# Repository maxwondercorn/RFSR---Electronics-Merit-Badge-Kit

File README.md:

Electronics Merit Badge Kit
==================================

Small ATtiny (Arduino IDE Compatible) microcontroller based kit used to teach Electronics Merit Badge at Resica Falls Scout Reservation.  Once assembled and functional, the kit allows selection of various LED display modes (Flickering Candle, Nightlight, Flashlight, Etc.) by rotating the on-board potentiometer.  Kit design is intended to meet all relevant badge requirements and expose scouts to a variety of component types at the lowest cost possible.

Repository Contents
-------------------

* **/Hardware** - Eagle Schematic / PCB Layouts & Bill Of Materials
    - PCB silkscreen periodically updated to match summer camp staff members currently teaching Electronics Merit Badge at Resica Falls Scout Reservation.
    - Bill Of Materials includes vendors / part numbers from the last production run.
* **/Software** - Demo Arduino sketch for the kit.  Code is intended to be easy to understand for beginners.
* **/Images** - Images of the kit, both assembled and in parts.

Firmware Programming
-------------------

As of the 2017 summer camp season, kit firmware is programmed using the following tools:

#### Hardware
An [Arduino Uno](https://store.arduino.cc/usa/arduino-uno-rev3) and an [AVR Programmer Shield](http://www.electrodragon.com/w/AVR_Programmer_Arduino_Shield) with ZIF socket.

Image of programming rig: [/Images/ElectronicsMBProgrammingRig.jpg](https://raw.githubusercontent.com/crossfireprod/RFSR---Electronics-Merit-Badge-Kit/master/Images/ElectronicsMBProgrammingRig.jpg)

#### Software
The Arduino Uno is used as an in system programmer (ISP) through use of the [ArduinoISP](https://github.com/arduino/ArduinoISP) sketch packaged with [Arduino 1.8.3](https://www.arduino.cc/en/main/software) to program the ATtiny 45/85 targets.  ATtiny core files available from [David Mellis' GitHub Repository](https://github.com/damellis/attiny), using [full instructions published by high-low tech](http://highlowtech.org/?p=1695) allow the ATtiny AVR microcontrollers used in the kits to be programmed directly from the Arduino IDE.

License
-------------------

All contents of this repository are released under [Creative Commons Share-alike 4.0](http://creativecommons.org/licenses/by-sa/4.0/).

Kit Design By: [*ZachCross.com*](https://ZachCross.com)

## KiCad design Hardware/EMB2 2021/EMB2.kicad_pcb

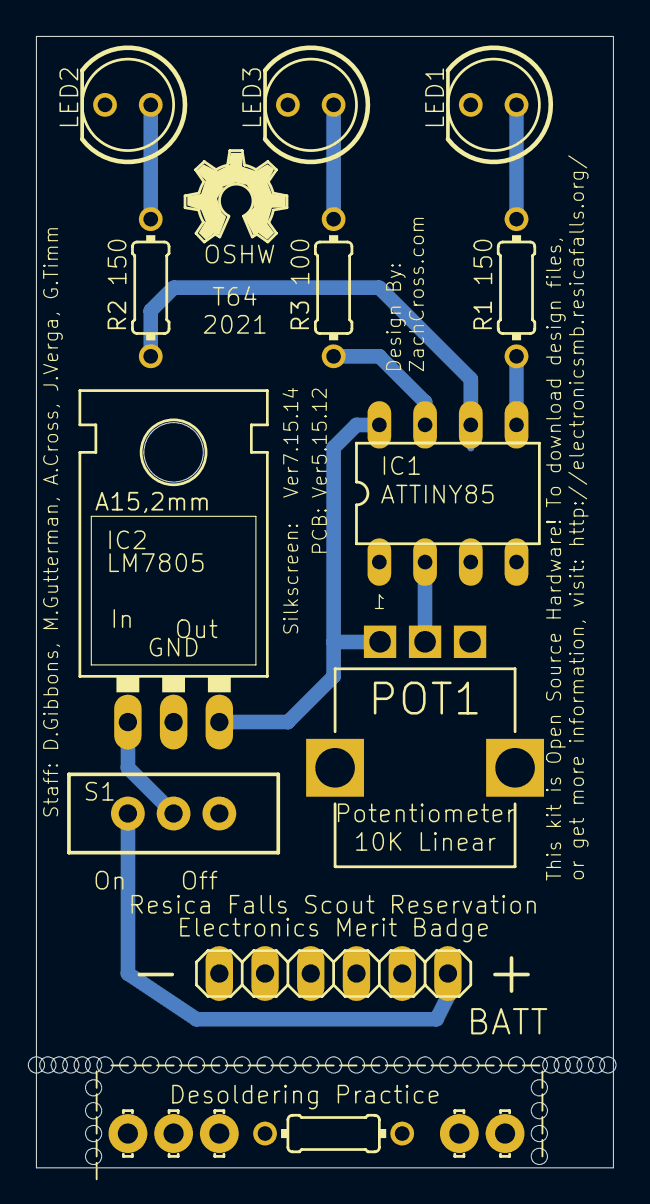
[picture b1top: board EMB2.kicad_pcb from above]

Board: 2 copper layers, 32.1 x 62.9 mm, 58 parts (0 on the bottom side), 4 nets.

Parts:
10K_LIN_POT: 10K Lin Pot; PTV09A-4025F-B103
7805: 78XXL
@HOLE0, @HOLE1, @HOLE2, @HOLE3, @HOLE4, @HOLE5, @HOLE6, @HOLE7, @HOLE8, @HOLE9, @HOLE10, @HOLE11, @HOLE12, @HOLE13, @HOLE14, @HOLE15, @HOLE16, @HOLE17, @HOLE18, @HOLE19, @HOLE20, @HOLE21, @HOLE22, @HOLE23, @HOLE24, @HOLE25, @HOLE26, @HOLE27, @HOLE28, @HOLE29, @HOLE30, @HOLE31, @HOLE32, @HOLE33, @HOLE34, @HOLE35, @HOLE36, @HOLE37, @HOLE38, @HOLE39: (no value)
E$2: 1X06
E$3: OSHW_FILLX200_NOTEXT
E$5, E$6, E$7, E$8, E$9: LSP11
IC1: ATTiny85; DIL08
L1, L2: Yel; LED5MM
L3: Wht; LED5MM
PRACTICE: 0204_7
R1, R2: 150; 0204_7
R3: 100; 0204_7
S1: SWITCH-SPSTPTH; SWITCH-SPDT

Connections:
GND: 7805.GND, E$2.1, L1.K, L2.K, L3.K
unnamed: IC1.5, R1.1
unnamed: IC1.6, R2.1
unnamed: IC1.7, R3.1

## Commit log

2015-07-29 Electronics_MB_7_14_14.pde
    Updated the code by adding a test sequence at start up.
2017-02-03 Added supporting documentation.
2017-07-08 Added image of example programming rig.
2017-07-08 Added firmware programming information to README
2017-07-08 Fixed markdown typos.
2017-07-08 Fixed link syntax typo.
2017-07-08 Style changes
2017-07-08 Changed link display syntax.
2021-11-23 feat: Converted to KiCad
2021-11-23 chore: Eagle project imported
    Rnamed so it could be imported into KiCad
2021-11-23 Create gerber file
2021-11-23 Added missing keepout zone
